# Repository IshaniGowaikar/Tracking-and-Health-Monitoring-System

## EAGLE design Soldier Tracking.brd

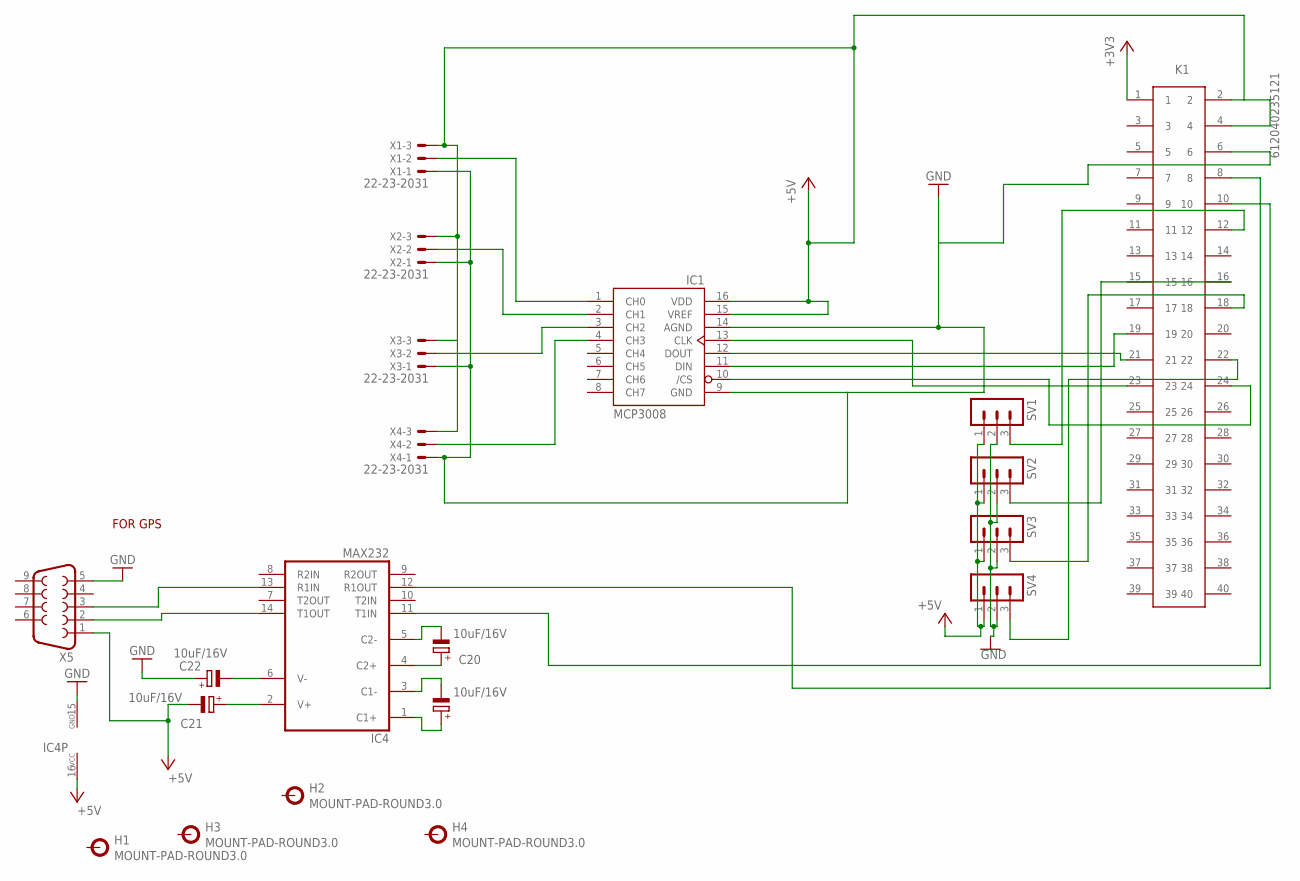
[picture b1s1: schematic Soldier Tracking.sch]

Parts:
C17, C20, C21, C22: 10uF/16V; E2,5-6
H1, H2, H3, H4: MOUNT-PAD-ROUND3.0; 3,0-PAD
IC1: MCP3008; DIL16
IC4: MAX232; DIL16
K1: 612040235121
SV1, SV2, SV3, SV4: MA03-1
X1, X2, X3, X4: 22-23-2031
X5: F09HP

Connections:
+3V3: K1.1
+5V: C21.-, IC1.15 (VREF), IC1.16 (VDD), IC4.16 (VCC), K1.2, K1.4, SV1.1, SV2.1, SV3.1, SV4.1, X1.3, X2.3, X3.3, X4.3, X5.1
GND: C22.+, IC1.9 (GND), IC1.14 (AGND), IC4.15 (GND), K1.6, SV1.2, SV2.2, SV3.2, SV4.2, X1.1, X2.1, X3.1, X4.1, X5.5
unnamed: IC1.1 (CH0), X1.2
unnamed: IC1.2 (CH1), X2.2
unnamed: IC1.3 (CH2), X3.2
unnamed: IC1.4 (CH3), X4.2
unnamed: K1.12, SV1.3
unnamed: K1.16, SV2.3
unnamed: K1.18, SV3.3
unnamed: K1.22, SV4.3
unnamed: IC1.10 (/CS), K1.24
unnamed: IC1.11 (DIN), K1.19
unnamed: IC1.12 (DOUT), K1.21
unnamed: IC1.13 (CLK), K1.23
unnamed: IC4.11 (T1IN), K1.8
unnamed: IC4.12 (R1OUT), K1.10
unnamed: C17.+, IC4.1 (C1+)
unnamed: C17.-, IC4.3 (C1-)
unnamed: C20.+, IC4.4 (C2+)
unnamed: C20.-, IC4.5 (C2-)
unnamed: C21.+, IC4.2 (V+)
unnamed: C22.-, IC4.6 (V-)
unnamed: IC4.14 (T1OUT), X5.2
unnamed: IC4.13 (R1IN), X5.3

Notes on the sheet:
FOR GPS

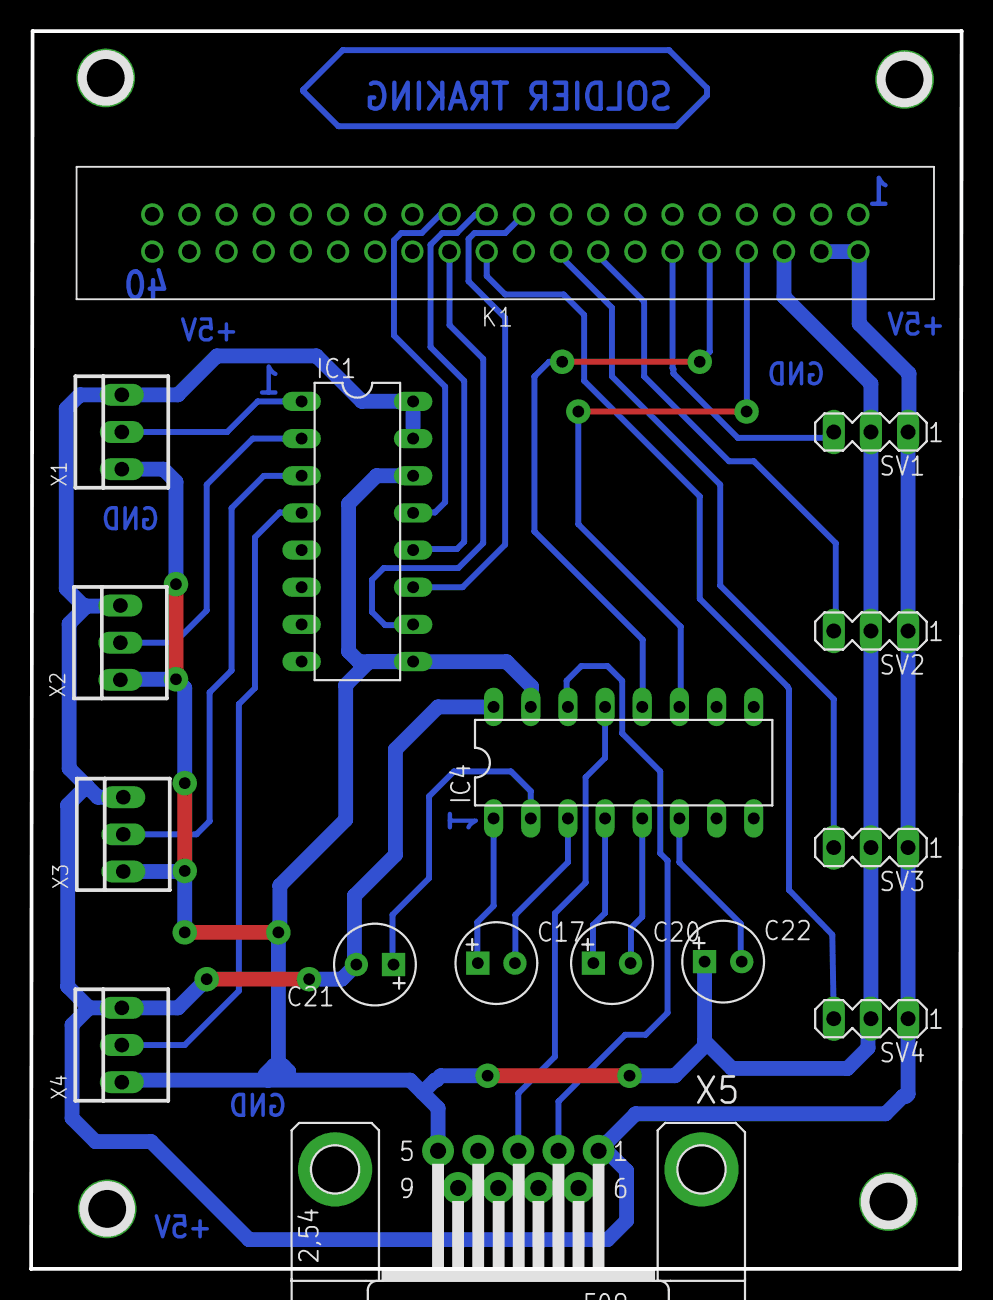
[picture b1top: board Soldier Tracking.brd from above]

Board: 2 copper layers, 63.6 x 84.6 mm, 20 parts (0 on the bottom side), 24 nets.

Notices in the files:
parts and their libraries:
Wire_to_Board_Connectors_rev15d: Copyright: Würth Elektronik
